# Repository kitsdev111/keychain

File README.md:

# Solar-Charged Ultra-Low-Power LED Fidget Keychain

A manufacturing-ready, ultra-compact (**20.0 × 32.0 mm**) solar-harvesting LED fidget keychain powered by a **Microchip ATtiny1616-MNR** (`1.8 V–5.5 V`), a **5.5 V 1.0 F supercapacitor**, and a **mini 5.5 V epoxy solar cell**.

---

## Repository Structure

```text
├── hardware/                 # KiCad 8 schematic, PCB layout, and project files
│   ├── solar_fidget.kicad_pro
│   ├── solar_fidget.kicad_sch
│   └── solar_fidget.kicad_pcb
├── pcba_production/          # PCBWay Turn-Key PCBA manufacturing package
│   ├── gerbers.zip           # RS-274X Gerbers + Excellon PTH/NPTH drills
│   ├── BOM_PCBWay.csv        # PCBWay formatted BOM (LCSC part numbers, THT/DNP marked)
│   ├── CPL_PCBWay.csv        # Top-side SMD Pick-and-Place coordinates (mm)
│   ├── Assembly_Drawing.pdf  # Dual-side assembly & polarity guide
│   └── Assembly_Drawing.svg
├── firmware/                 # PlatformIO / Arduino (megaTinyCore) firmware @ 1 MHz
│   ├── platformio.ini
│   ├── src/main.cpp          # 5 fidget modes + ~100 nA SLEEP_MODE_PWR_DOWN
│   └── README_FLASHING.md    # SerialUPDI flashing & fuse guide
├── enclosure/                # Parametric 3D-printable snap-fit keychain shell
│   ├── solar_fidget_enclosure.scad
│   ├── top_bezel.stl         # 0.4 mm diffuser window + button collar (print roof-down)
│   ├── bottom_tray.stl       # 25.4x30.4 mm solar pocket + supercap cavity + lanyard loop
│   └── button_plunger.stl    # Captive tactile switch actuator pin
└── sourcing/
    └── aliexpress_parts.md   # Sourcing guide for solar panel, supercap, UPDI & hardware
```

---

## Key Hardware & Design Highlights

* **MCU:** `ATtiny1616-MNR` (VQFN-20, 3×3 mm, LCSC `C507118`) running at **1 MHz internal clock** directly from the supercapacitor (`1.8 V–5.5 V` unregulated).
* **Solar Harvesting & Protection:**
  * `BAT54WS` (SOD-323) low-Vf Schottky reverse-blocking diode (`SOL+` → `VCC`).
  * `BZX84C5V1` (SOT-23) 5.1 V Zener shunt clamp protecting the MCU and supercapacitor.
  * `5.5 V 1.0 F` THT coin supercapacitor (`7.5 mm` pitch) + 2× optional `1210` parallel MLCC/supercap pads (`DNP`) + `100 nF` `0603` decoupling at `VDD`/`GND`.
* **Display & UI:** 7× `0603` Red LEDs (`Vf ≈ 2.0 V`, individual `680 Ω` resistors) in a 2-3-2 hexagonal rosette (`LED1–LED6` on hardware `TCA0` PWM, `LED7` on hardware `TCB0` PWM) + `3×4 mm` SMD tactile button on async pin-change interrupt `PC2`.
* **PCB Finish & Custom Watermark:**
  * **PCBWay Spec:** 2-layer `1.6 mm` FR4, **Matte Black** solder mask, **White** silkscreen, **ENIG (Gold)** surface finish recommended so the exposed bare-copper **Fox Logo + `kitsdev` watermark** (`F.Cu` + `F.Mask` opening) and `VCC`/`GND`/`UPDI` bottom pogo pads shine cleanly and resist oxidation.
  * **Single-Sided SMD PCBA:** All 19 assembled SMD components are on `F.Cu` (`Top`), keeping PCBWay SMT assembly costs minimal.

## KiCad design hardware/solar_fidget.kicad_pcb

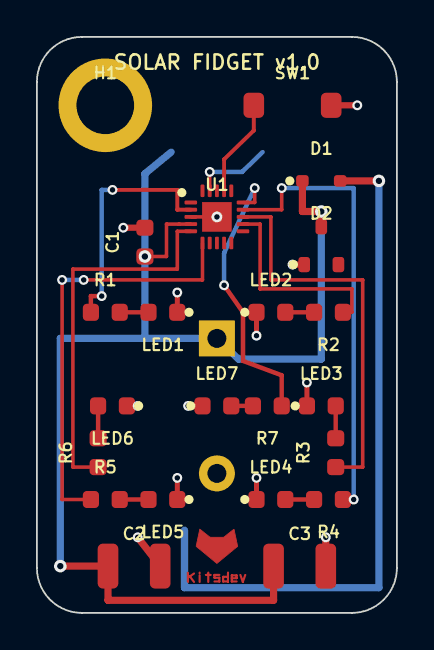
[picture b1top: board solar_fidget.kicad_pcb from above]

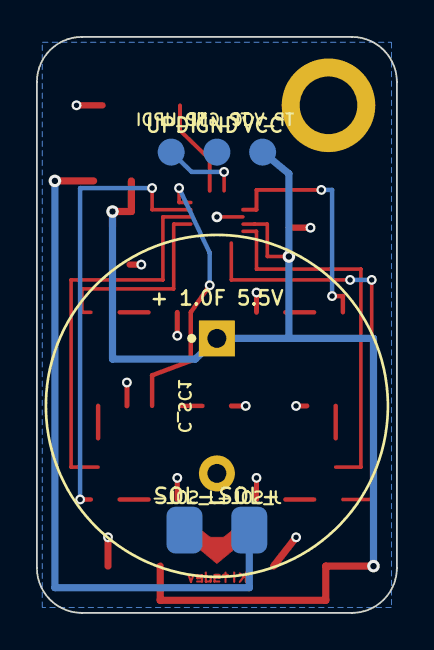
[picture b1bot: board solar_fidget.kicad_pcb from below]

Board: 2 copper layers, 20.0 x 32.0 mm, 28 parts (6 on the bottom side), 19 nets.

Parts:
C1: 100nF; C_0603_1608Metric
C2, C3: DNP (Opt 1210); C_1210_3225Metric
C_SC1: 1.0F 5.5V; CP_Radial_D19.5mm_P7.50mm
D1: BAT54WS; D_SOD-323
D2: BZX84C5V1; SOT-23
H1: Keychain_M3.2; MountingHole_3.2mm_M3_Pad_TopBottom
J_SOL+: SOL+; SolderWirePad_1x01_SMD_2.0x2.6mm
J_SOL-: GND; SolderWirePad_1x01_SMD_2.0x2.6mm
LED1, LED2, LED3, LED4, LED5, LED6, LED7: LED_RED_0603; LED_0603_1608Metric
R1, R2, R3, R4, R5, R6, R7: 680R; R_0603_1608Metric
SW1: SW_TACT_3x4; SW_SPST_PTS810
TP_GND: GND; TestPoint_Pad_D1.5mm
TP_UPDI: UPDI; TestPoint_Pad_D1.5mm
TP_VCC: VCC; TestPoint_Pad_D1.5mm
U1: ATtiny1616-MNR; QFN-20-1EP_3x3mm_P0.4mm_EP1.65x1.65mm

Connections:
BTN_SW1: SW1.1, U1.17
GND: C1.2, C2.2, C3.2, C_SC1.2, D2.1, J_SOL-.1, LED1.1, LED2.1, LED3.1, LED4.1, LED5.1, LED6.1, LED7.1, SW1.2, TP_GND.1, U1.3, U1.21
LED1_A: LED1.2, R1.2
LED1_DRV: R1.1, U1.2
LED2_A: LED2.2, R2.2
LED2_DRV: R2.1, U1.12
LED3_A: LED3.2, R3.2
LED3_DRV: R3.1, U1.13
LED4_A: LED4.2, R4.2
LED4_DRV: R4.1, U1.14
LED5_A: LED5.2, R5.2
LED5_DRV: R5.1, U1.6
LED6_A: LED6.2, R6.2
LED6_DRV: R6.1, U1.5
LED7_A: LED7.2, R7.2
LED7_DRV: R7.1, U1.15
SOL+: D1.2, J_SOL+.1
UPDI: TP_UPDI.1, U1.19
VCC: C1.1, C2.1, C3.1, C_SC1.1, D1.1, D2.3, TP_VCC.1, U1.4

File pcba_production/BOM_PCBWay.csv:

Item #,Designator,Qty,Manufacturer,Mfg Part #,Description / Value,Package / Footprint,Type [SMD/THT],LCSC / Supplier Part #
1,U1,1,Microchip Technology,ATTINY1616-MNR,"8-bit AVR MCU, 16KB Flash, 1.8V-5.5V, VQFN-20 (3x3mm)",VQFN-20 (3x3mm),SMD,C507118
2,C1,1,YAGEO,CC0603KRX7R9BB104,MLCC 100nF 50V X7R +/-10% 0603,0603,SMD,C14663
3,D1,1,Diodes Incorporated,BAT54WS-7-F,"Schottky Barrier Diode 30V 200mA Low-Vf, SOD-323",SOD-323,SMD,C668868
4,D2,1,onsemi,SZBZX84C5V1LT1G,"Zener Diode 5.1V 225mW Voltage Clamp, SOT-23",SOT-23,SMD,C150218
5,SW1,1,hanxia,HX 3x4x2-2P-1.6N,SMD Tactile Push Button 3x4x2mm 160gf SPST-NO,SMD-2P (3x4mm),SMD,C49234124
6,"LED1, LED2, LED3, LED4, LED5, LED6, LED7",7,KENTO,KT-0603R,"Red 0603 SMD LED (620-630nm, Vf ~2.0V)",0603,SMD,C2286
7,"R1, R2, R3, R4, R5, R6, R7",7,UNI-ROYAL,0603WAF6800T5E,Thick Film Resistor 680 Ohm +/-1% 1/10W 0603,0603,SMD,C23228
8,C_SC1,1,Viking / Kamcap,SC5V5H105Z,"5.5V 1.0F Coin-Type EDLC Supercapacitor (7.5mm Pitch, Hand-Soldered THT)",Radial Coin Ø19.2x4.8mm P7.5mm,THT (DNP for SMT),N/A (Hand-Solder / AliExpress)
9,"C2, C3",2,Optional,DNP,Optional Parallel High-Cap 1210 MLCC / SMD Supercap Footprint (Do Not Populate),1210,DNP,DNP
10,SOL1,1,Generic,SOLAR-5V-25X30,5V/5.5V Mini Epoxy Solar Panel ~25x30mm (External Wire-Soldered to SOL+/SOL-),25x30x2.5mm Module,DNP (External),N/A (AliExpress)
